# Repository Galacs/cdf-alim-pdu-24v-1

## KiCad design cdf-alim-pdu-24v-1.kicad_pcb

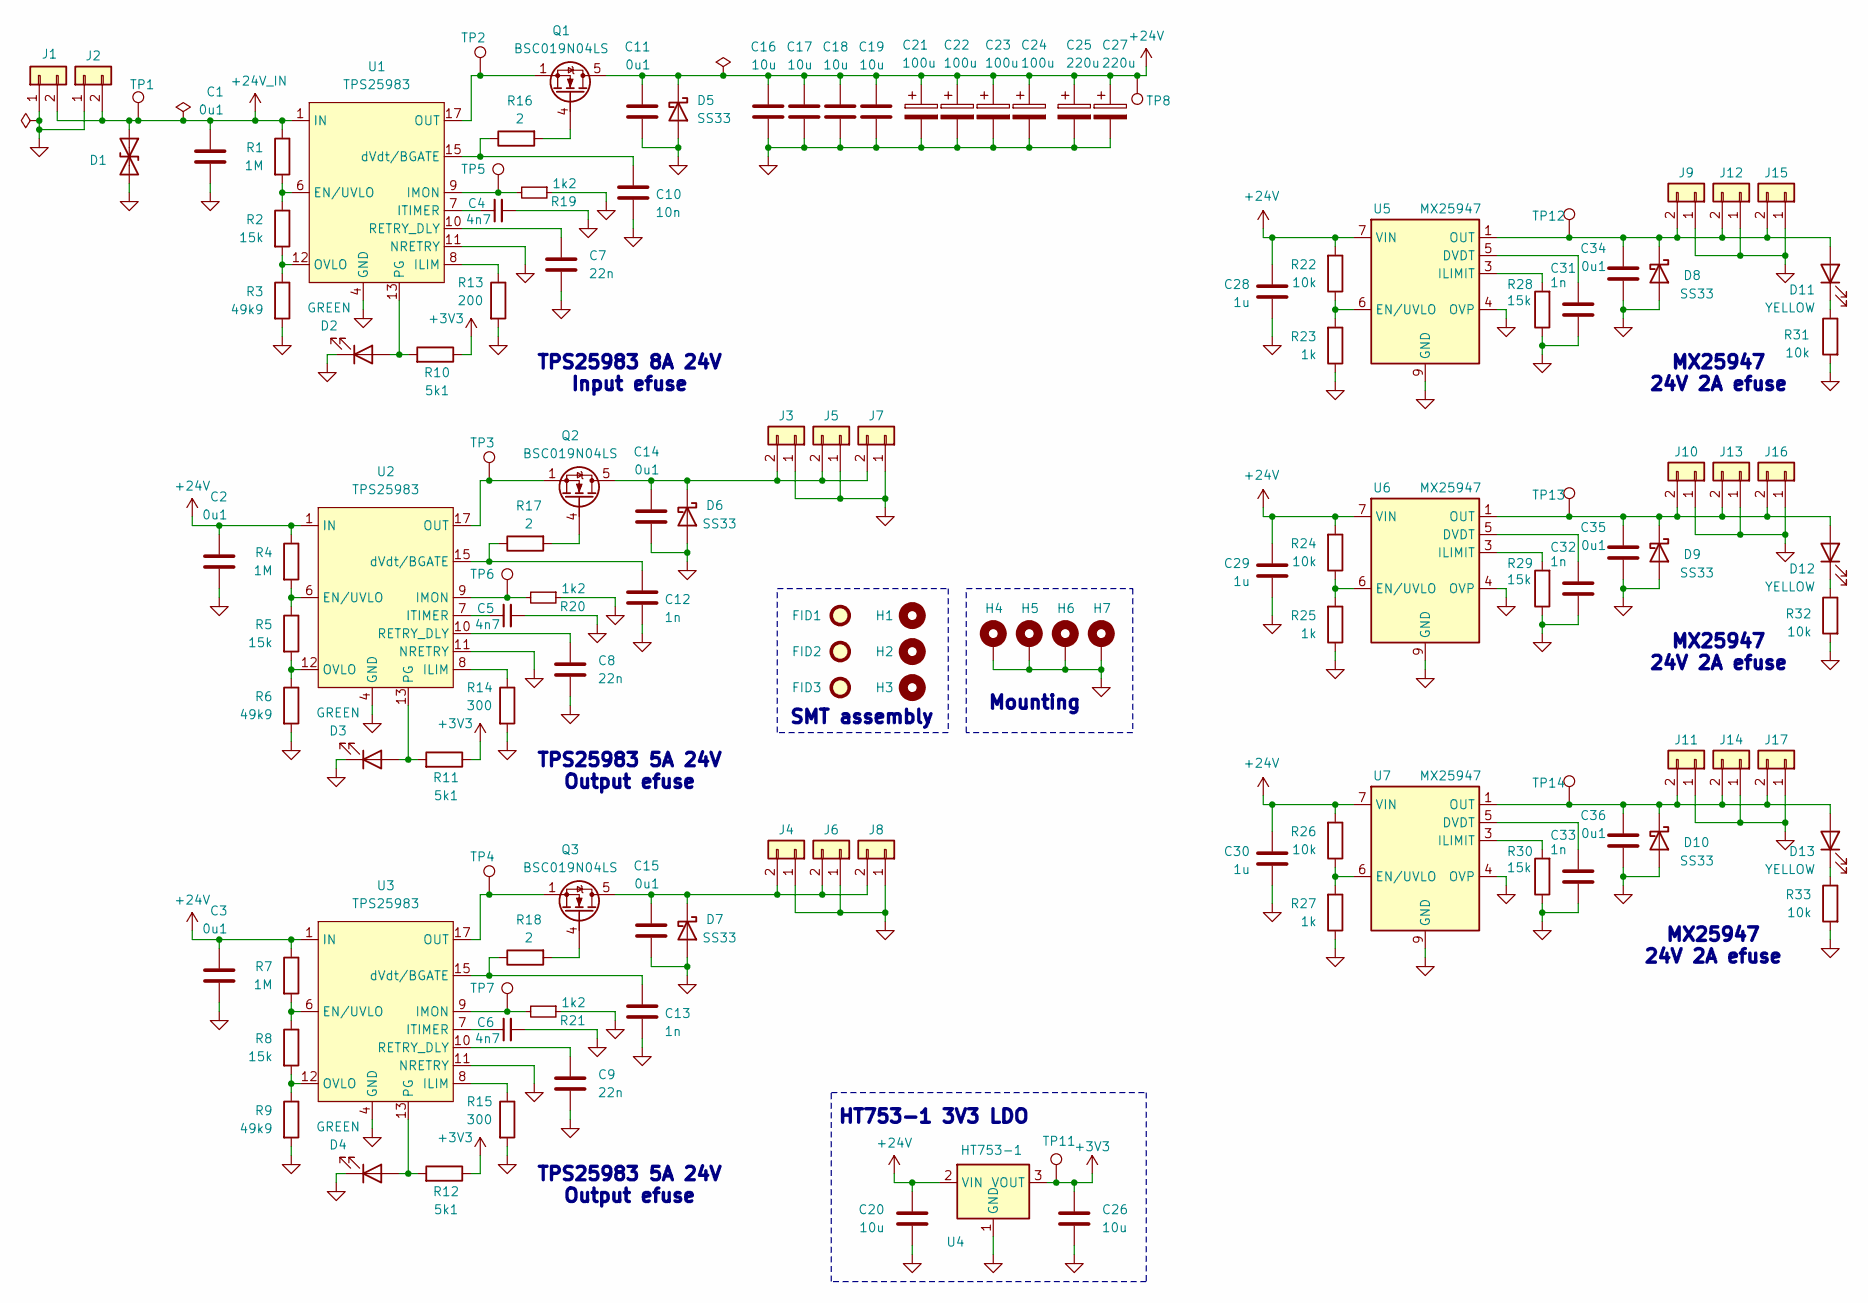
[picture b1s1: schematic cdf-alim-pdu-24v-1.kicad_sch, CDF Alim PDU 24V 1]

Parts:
C1, C2, C3, C11, C14, C15, C34, C35, C36: 0u1; C_0402_1005Metric; Manufacturer Part Number CL05B104KB54PNC; JLCPCB Part # C307331
C4, C5, C6: 4n7; C_0402_1005Metric; Manufacturer Part Number 0402B472K500NT; JLCPCB Part # C1538
C7, C8, C9: 22n; C_0402_1005Metric; Manufacturer Part Number 0402B223K500NT; JLCPCB Part # C1532
C10: 10n; C_0603_1608Metric; Manufacturer Part Number 0603B103K500NT; JLCPCB Part # C57112
C12, C13: 1n; C_0603_1608Metric; Manufacturer Part Number CL10B102KB8NNNC; JLCPCB Part # C1588
C16, C17, C18, C19: 10u; C_1206_3216Metric; Manufacturer Part Number CL31A106KBHNNNE; JLCPCB Part # C13585
C20, C26: 10u; C_0805_2012Metric; Manufacturer Part Number GRM21BR61H106KE43L; JLCPCB Part # C440198
C21, C22, C23, C24: 100u; CP_Elec_8x10; Manufacturer Part Number RHS1V101MCN1GS; JLCPCB Part # C2162472
C25, C27: 220u; CP_Elec_10x10; Manufacturer Part Number UWT1H221MNL1GS; JLCPCB Part # C125977
C28, C29, C30: 1u; C_0402_1005Metric; Manufacturer Part Number CL05A105KA5NQNC; JLCPCB Part # C52923
C31, C32, C33: 1n; C_0402_1005Metric; Manufacturer Part Number 0402B102K500NT; JLCPCB Part # C1523
D1: SMAJ26CA; D_SMA; Manufacturer Part Number SMAJ26CA; JLCPCB Part # C19077544
D2, D3, D4: GREEN; LED_0805_2012Metric; Manufacturer Part Number KT-0805G; JLCPCB Part # C2297
D5, D6, D7, D8, D9, D10: SS33; D_SMA; Manufacturer Part Number SS33; JLCPCB Part # C28646294
D11, D12, D13: YELLOW; LED_0805_2012Metric; Manufacturer Part Number KT-0805Y; JLCPCB Part # C2296
FID1, FID2, FID3: Fiducial; Fiducial_1mm_Mask2mm
H1, H2, H3: MountingHole; ToolingHole_1.152mm
H4, H5, H6, H7: MountingHole_Pad; MountingHole_3.2mm_M3_Pad_Via
J1: Conn_01x02; AMASS_XT30PW-M_1x02_P2.50mm_Horizontal; Manufacturer Part Number XT30PW-M30.G.Y; JLCPCB Part # C431092
J2: Conn_01x02; AMASS_XT30PW-F_1x02_P2.50mm_Horizontal; Manufacturer Part Number XT30PW-F20.G.Y; JLCPCB Part # C2913282
J3, J4, J5, J6, J7, J8, J9, J10, J11, J12, J13, J14, J15, J16, J17: Conn_01x02; JST_XH_B2B-XH-A_1x02_P2.50mm_Vertical; Manufacturer Part Number B2B-XH-A(LF)(SN); JLCPCB Part # C158012
Q1, Q2, Q3: BSC019N04LS; TDSON-8-1; Manufacturer Part Number BSC019N04LS; JLCPCB Part # C534301
R1, R4, R7: 1M; R_0402_1005Metric; Manufacturer Part Number 0402WGF1004TCE; JLCPCB Part # C26083
R2, R5, R8, R28, R29, R30: 15k; R_0402_1005Metric; Manufacturer Part Number 0402WGF1502TCE; JLCPCB Part # C25756
R3, R6, R9: 49k9; R_0603_1608Metric; Manufacturer Part Number 0603WAF4992T5E; JLCPCB Part # C23184
R10, R11, R12: 5k1; R_0402_1005Metric; Manufacturer Part Number 0402WGF5101TCE; JLCPCB Part # C25905
R13: 200; R_0402_1005Metric; Manufacturer Part Number 0402WGF2000TCE; JLCPCB Part # C25087
R14, R15: 300; R_0402_1005Metric; Manufacturer Part Number 0402WGF3000TCE; JLCPCB Part # C25102
R16, R17, R18: 2; R_0603_1608Metric; Manufacturer Part Number 0603WAF200KT5E; JLCPCB Part # C22977
R19, R20, R21: 1k2; R_0603_1608Metric; Manufacturer Part Number 0603WAF1201T5E; JLCPCB Part # C22765
R22, R24, R26, R31, R32, R33: 10k; R_0402_1005Metric; Manufacturer Part Number 0402WGF1002TCE; JLCPCB Part # C25744
R23, R25, R27: 1k; R_0402_1005Metric; Manufacturer Part Number 0402WGF1001TCE; JLCPCB Part # C11702
TP1, TP2, TP3, TP4, TP5, TP6, TP7, TP8, TP11, TP12, TP13, TP14: TestPoint; TestPoint_Pad_D2.0mm
U1, U2, U3: TPS25983; Texas_RGE0024M_VQFN-24-1EP_4x4mm_P0.5mm_ThermalVias; Manufacturer Part Number TPS259830ONRGER; JLCPCB Part # C20611808
U4: HT753-1; SOT-89-3; Manufacturer Part Number HT7533-1; JLCPCB Part # C14289
U5, U6, U7: MX25947; TI_SO-PowerPAD-8_ThermalVias; Manufacturer Part Number MX25947ES; JLCPCB Part # C5875698

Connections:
+3V3: C26.1, R10.1, R11.1, R12.1, TP11.1 (1_1), U4.3 (VOUT)
+24V: C2.1, C3.1, C11.1, C16.1, C17.1, C18.1, C19.1, C20.1, C21.1, C22.1, C23.1, C24.1, C25.1, C27.1, C28.2, C29.2, C30.2, D5.1 (K), Q1.5 (D), R4.1, R7.1, R22.2, R24.2, R26.2, TP8.1 (1_1), U2.1 (IN), U2.2 (IN), U2.3 (IN), U2.16 (IN), U2.25 (IN), U3.1 (IN), U3.2 (IN), U3.3 (IN), U3.16 (IN), U3.25 (IN), U4.2 (VIN), U5.7 (VIN), U5.8 (VIN), U6.7 (VIN), U6.8 (VIN), U7.7 (VIN), U7.8 (VIN)
+24V_IN: C1.1, D1.1 (A1), J1.2, J2.2, R1.1, TP1.1 (1_1), U1.1 (IN), U1.2 (IN), U1.3 (IN), U1.16 (IN), U1.25 (IN)
GND: C1.2, C2.2, C3.2, C4.2, C5.2, C6.2, C7.2, C8.2, C9.2, C10.1, C11.2, C12.1, C13.1, C14.2, C15.2, C16.2, C17.2, C18.2, C19.2, C20.2, C21.2, C22.2, C23.2, C24.2, C25.2, C26.2, C27.2, C28.1, C29.1, C30.1, C31.2, C32.2, C33.2, C34.2, C35.2, C36.2, D1.2 (A2), D2.1 (K), D3.1 (K), D4.1 (K), D5.2 (A), D6.2 (A), D7.2 (A), D8.2 (A), D9.2 (A), D10.2 (A), H4.1 (1_1), H5.1 (1_1), H6.1 (1_1), H7.1 (1_1), J1.1, J2.1, J3.1, J4.1, J5.1, J6.1, J7.1, J8.1, J9.1, J10.1, J11.1, J12.1, J13.1, J14.1, J15.1, J16.1, J17.1, R3.2, R6.2, R9.2, R13.2, R14.2, R15.2, R19.1, R20.1, R21.1, R23.1, R25.1, R27.1, R28.1, R29.1, R30.1, R31.2, R32.2, R33.2, U1.4 (GND), U1.5 (GND), U1.11 (NRETRY), U1.14 (GND), U1.26 (GND), U2.4 (GND), U2.5 (GND), U2.11 (NRETRY), U2.14 (GND), U2.26 (GND), U3.4 (GND), U3.5 (GND), U3.11 (NRETRY), U3.14 (GND), U3.26 (GND), U4.1 (GND), U5.4 (OVP), U5.9 (GND), U6.4 (OVP), U6.9 (GND), U7.4 (OVP), U7.9 (GND)
unnamed: D2.2 (A), R10.2, U1.13 (PG)
unnamed: D3.2 (A), R11.2, U2.13 (PG)
unnamed: D4.2 (A), R12.2, U3.13 (PG)
unnamed: C14.1, D6.1 (K), J3.2, J5.2, J7.2, Q2.5 (D)
unnamed: C15.1, D7.1 (K), J4.2, J6.2, J8.2, Q3.5 (D)
unnamed: C36.1, D10.1 (K), D13.2 (A), J11.2, J14.2, J17.2, TP14.1 (1_1), U7.1 (OUT), U7.2 (OUT)
unnamed: C34.1, D8.1 (K), D11.2 (A), J9.2, J12.2, J15.2, TP12.1 (1_1), U5.1 (OUT), U5.2 (OUT)
unnamed: D11.1 (K), R31.1
unnamed: C35.1, D9.1 (K), D12.2 (A), J10.2, J13.2, J16.2, TP13.1 (1_1), U6.1 (OUT), U6.2 (OUT)
unnamed: D12.1 (K), R32.1
unnamed: D13.1 (K), R33.1
unnamed: Q1.4 (G), R16.2
unnamed: Q1.1 (S), Q1.2 (S), Q1.3 (S), TP2.1 (1_1), U1.17 (OUT), U1.18 (OUT), U1.19 (OUT), U1.20 (OUT), U1.21 (OUT), U1.22 (OUT), U1.23 (OUT), U1.24 (OUT)
unnamed: Q2.4 (G), R17.2
unnamed: Q2.1 (S), Q2.2 (S), Q2.3 (S), TP3.1 (1_1), U2.17 (OUT), U2.18 (OUT), U2.19 (OUT), U2.20 (OUT), U2.21 (OUT), U2.22 (OUT), U2.23 (OUT), U2.24 (OUT)
unnamed: Q3.4 (G), R18.2
unnamed: Q3.1 (S), Q3.2 (S), Q3.3 (S), TP4.1 (1_1), U3.17 (OUT), U3.18 (OUT), U3.19 (OUT), U3.20 (OUT), U3.21 (OUT), U3.22 (OUT), U3.23 (OUT), U3.24 (OUT)
unnamed: R1.2, R2.1, U1.6 (EN/UVLO)
unnamed: R13.1, U1.8 (ILIM)
unnamed: R19.2, TP5.1 (1_1), U1.9 (IMON)
unnamed: C4.1, U1.7 (ITIMER)
unnamed: R2.2, R3.1, U1.12 (OVLO)
unnamed: C7.1, U1.10 (RETRY_DLY)
unnamed: C10.2, R16.1, U1.15 (dVdt/BGATE)
unnamed: R4.2, R5.1, U2.6 (EN/UVLO)
unnamed: R14.1, U2.8 (ILIM)
unnamed: R20.2, TP6.1 (1_1), U2.9 (IMON)
unnamed: C5.1, U2.7 (ITIMER)
unnamed: R5.2, R6.1, U2.12 (OVLO)
unnamed: C8.1, U2.10 (RETRY_DLY)
unnamed: C12.2, R17.1, U2.15 (dVdt/BGATE)
unnamed: R7.2, R8.1, U3.6 (EN/UVLO)
unnamed: R15.1, U3.8 (ILIM)
unnamed: R21.2, TP7.1 (1_1), U3.9 (IMON)
unnamed: C6.1, U3.7 (ITIMER)
unnamed: R8.2, R9.1, U3.12 (OVLO)
unnamed: C9.1, U3.10 (RETRY_DLY)
unnamed: C13.2, R18.1, U3.15 (dVdt/BGATE)
unnamed: C31.1, U5.5 (DVDT)
unnamed: R22.1, R23.2, U5.6 (EN/UVLO)
unnamed: R28.2, U5.3 (ILIMIT)
unnamed: C32.1, U6.5 (DVDT)
unnamed: R24.1, R25.2, U6.6 (EN/UVLO)
unnamed: R29.2, U6.3 (ILIMIT)
unnamed: C33.1, U7.5 (DVDT)
unnamed: R26.1, R27.2, U7.6 (EN/UVLO)
unnamed: R30.2, U7.3 (ILIMIT)

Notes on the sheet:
MX25947 24V 2A efuse
TPS25983 5A 24V Output efuse
HT753-1 3V3 LDO
TPS25983 8A 24V Input efuse
Mounting
SMT assembly

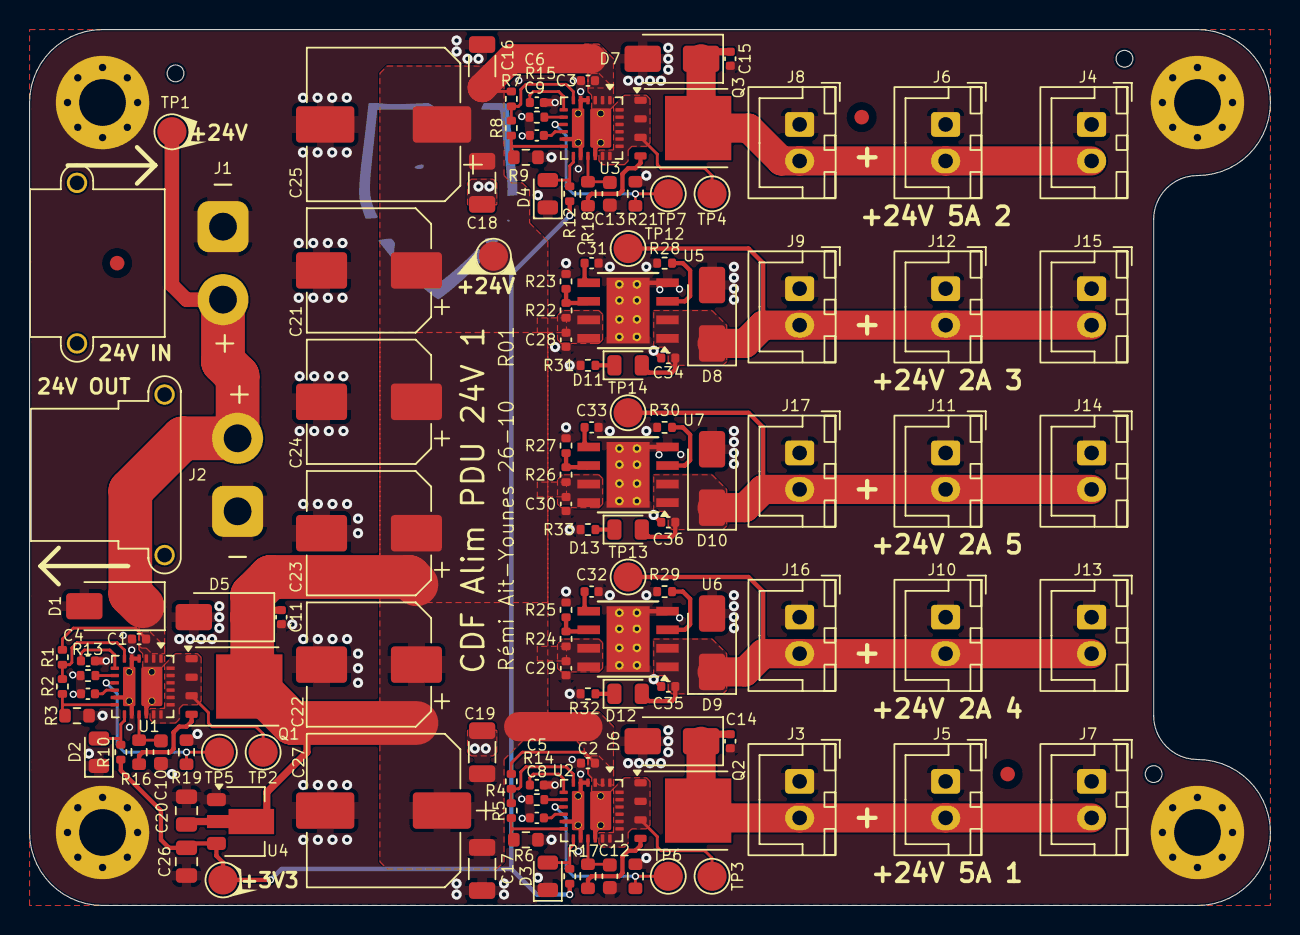
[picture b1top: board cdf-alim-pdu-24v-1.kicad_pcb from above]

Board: 2 copper layers, 85.0 x 60.0 mm, 131 parts (0 on the bottom side), 51 nets.

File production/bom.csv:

Designator,Footprint,Quantity,Value,LCSC Part #
"C1, C11, C14, C15, C2, C3, C34, C35, C36",0402,9,0u1,C307331
C10,0603,1,10n,C57112
"C12, C13",0603,2,1n,C1588
"C16, C17, C18, C19",1206,4,10u,C13585
"C20, C26",0805,2,10u,C440198
"C21, C22, C23, C24",CP_Elec_8x10,4,100u,C2162472
"C25, C27",CP_Elec_10x10,2,220u,C125977
"C28, C29, C30",0402,3,1u,C52923
"C31, C32, C33",0402,3,1n,C1523
"C4, C5, C6",0402,3,4n7,C1538
"C7, C8, C9",0402,3,22n,C1532
D1,D_SMA,1,SMAJ26CA,C19077544
"D10, D5, D6, D7, D8, D9",D_SMA,6,SS33,C28646294
"D11, D12, D13",0805,3,YELLOW,C2296
"D2, D3, D4",0805,3,GREEN,C2297
J1,AMASS_XT30PW-M_1x02_P2.50mm_Horizontal,1,Conn_01x02,C431092
"J10, J11, J12, J13, J14, J15, J16, J17, J3, J4, J5, J6, J7, J8, J9",JST_XH_B2B-XH-A_1x02_P2.50mm_Vertical,15,Conn_01x02,C158012
J2,AMASS_XT30PW-F_1x02_P2.50mm_Horizontal,1,Conn_01x02,C2913282
"Q1, Q2, Q3",TDSON-8-1,3,BSC019N04LS,C534301
"R1, R4, R7",0402,3,1M,C26083
"R10, R11, R12",0402,3,5k1,C25905
R13,0402,1,200,C25087
"R14, R15",0402,2,300,C25102
"R16, R17, R18",0603,3,2,C22977
"R19, R20, R21",0603,3,1k2,C22765
"R2, R28, R29, R30, R5, R8",0402,6,15k,C25756
"R22, R24, R26, R31, R32, R33",0402,6,10k,C25744
"R23, R25, R27",0402,3,1k,C11702
"R3, R6, R9",0603,3,49k9,C23184
"U1, U2, U3",Texas_RGE0024M_VQFN-24-1EP_4x4mm_P0.5mm_ThermalVias,3,TPS25983,C20611808
U4,SOT-89-3,1,HT753-1,C14289
"U5, U6, U7",TI_SO-PowerPAD-8_ThermalVias,3,MX25947,C5875698
